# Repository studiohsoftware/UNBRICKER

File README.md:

# UNBRICKER
# Unbrick an Arduino MKR1000 using another MKR1000.
Problem: The SAMD21 bootloader is in flash at address 0x0000, and can be blown away using a firmware flashing utility like bossac, 
if an offset of 0x2000 is not specified.
</br>
</br>
https://www.hackster.io/nicola-wrachien posted a helpful tutorial on unbricking the SAMD21, using a uChip as a host.
</br>
</br>
That project was easily converted to use an MKR1000 as a host. The result is this repository, which includes the Eagle brd file needed to 
produce a PCB, as well as the Arduino sketch that the MKR1000 host can use to flash the bricked MKR1000.
</br>
</br>
To prevent bricking using bossac, use this command line: </br>
bossac -p COM21 -e -w -v -R --offset=0x2000 firmwarefile.ino.bin

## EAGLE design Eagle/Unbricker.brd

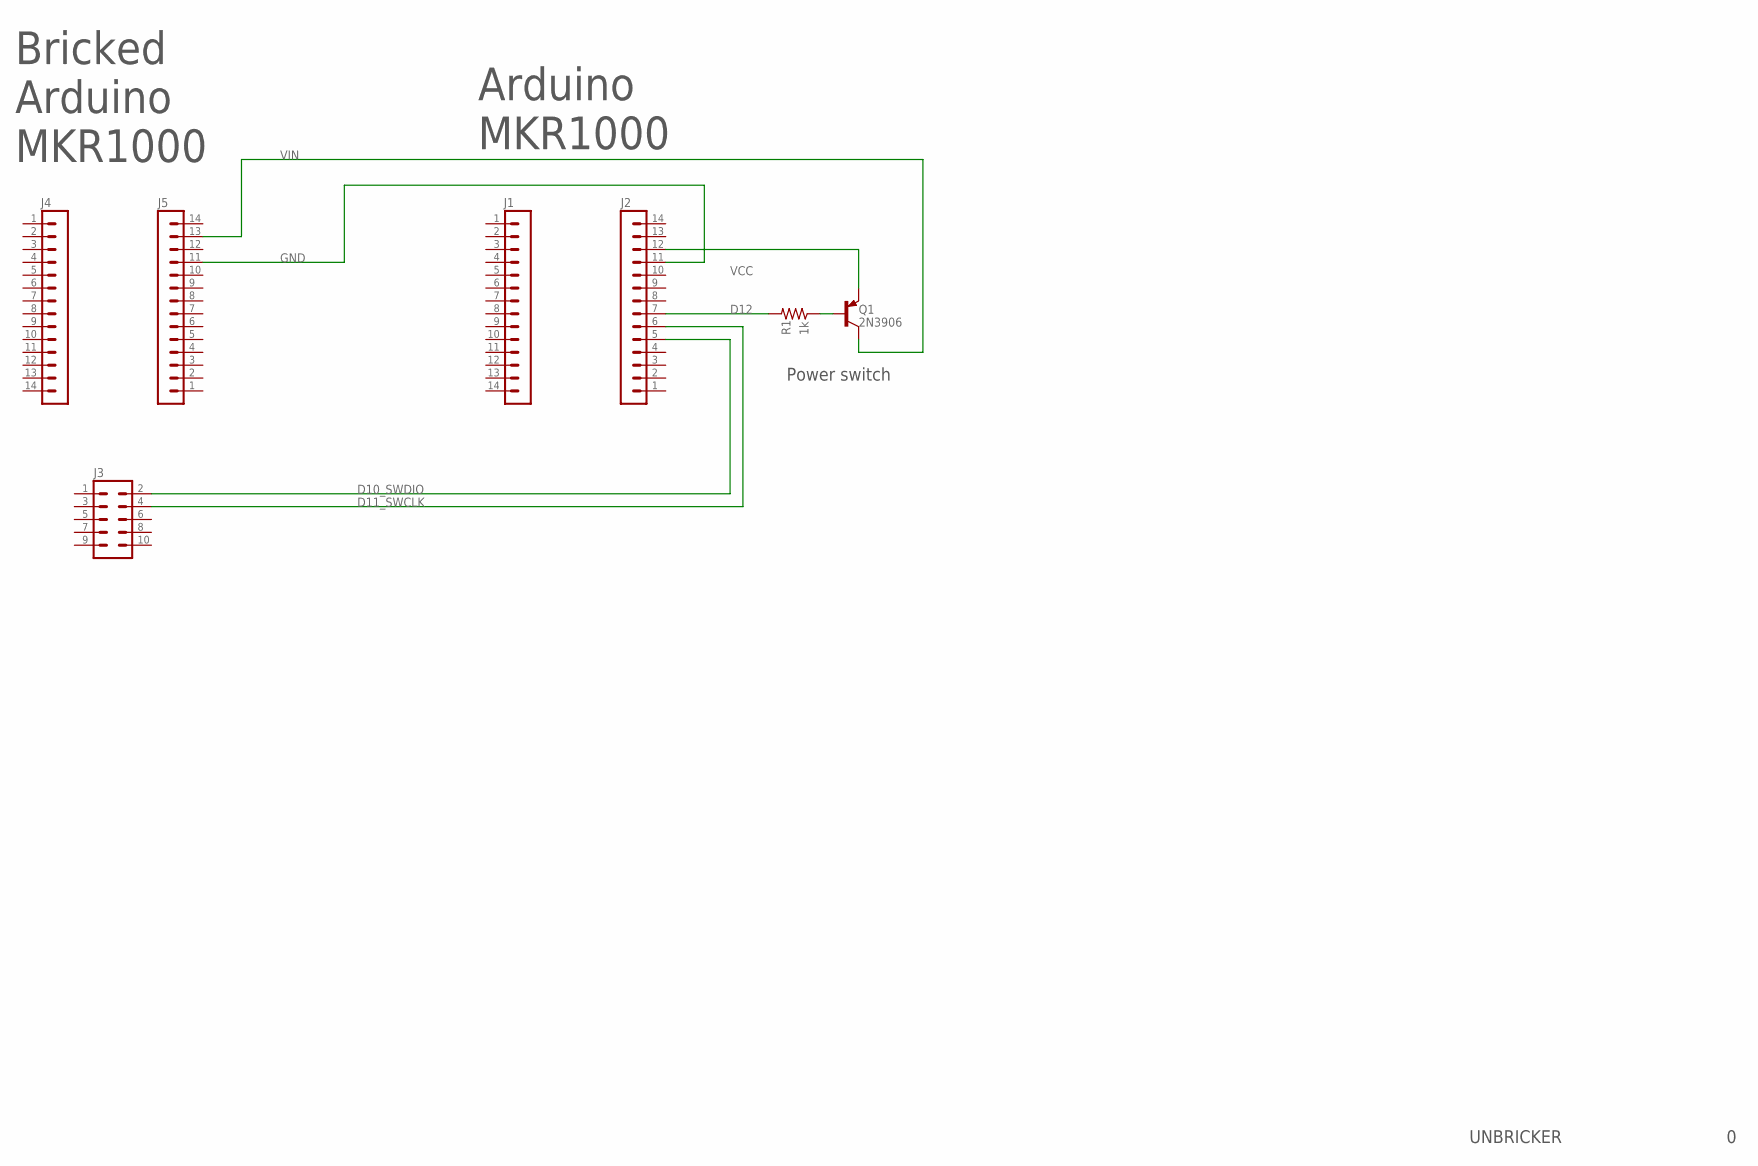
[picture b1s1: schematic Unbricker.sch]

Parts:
J1, J2, J4, J5: MA14-1
J3: M50-3600542; FCI-MINITEK127HDR-10
Q1: 2N3906; SOT23
R1: 1k; R0603

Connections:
D10_SWDIO: J2.5, J3.2
D11_SWCLK: J2.6, J3.4
D12: J2.7, R1.2
GND: J2.11, J5.11
unnamed: Q1.1 (B), R1.1
VCC: J2.12, Q1.3 (E)
VIN: J5.13, Q1.2 (C)

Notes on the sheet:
UNBRICKER
Arduino MKR1000
Bricked Arduino MKR1000
Power switch

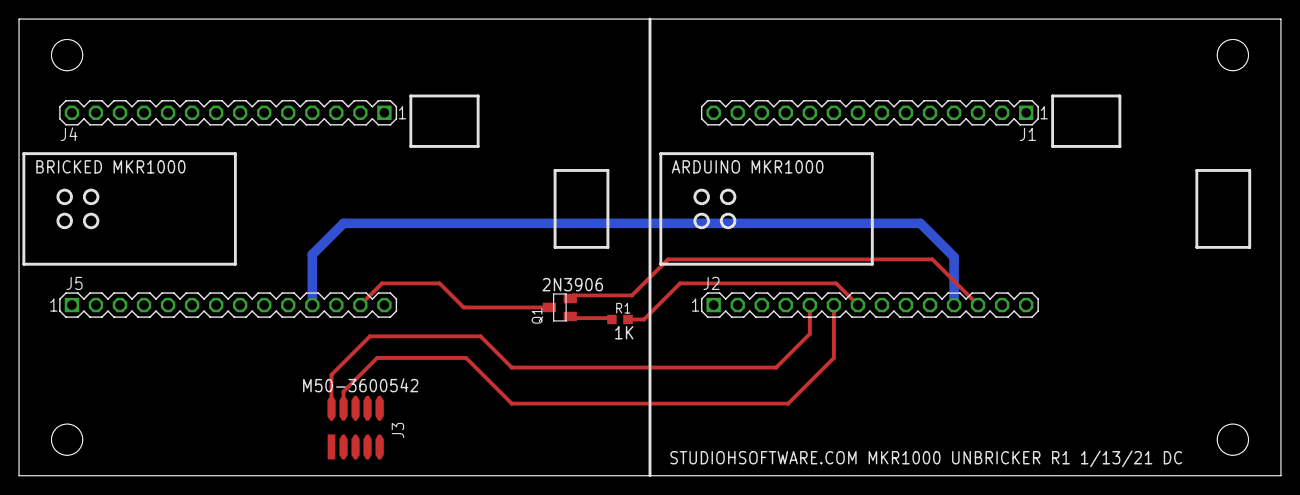
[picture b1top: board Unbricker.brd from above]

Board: 2 copper layers, 133.3 x 48.3 mm, 7 parts (0 on the bottom side), 7 nets.

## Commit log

2021-01-01 Based on Hackster.io SAMD21 Unbricker.
    https://www.hackster.io/nicola-wrachien
2021-01-01 Add LICENSE and README.md
2021-01-01 Fix typo
2021-01-13 Fix power line, add standoffs, etc.
